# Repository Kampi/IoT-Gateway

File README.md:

# IoT-Gateway

## Table of Contents

- [IoT-Gateway](#iot-gateway)
  - [Table of Contents](#table-of-contents)
  - [About](#about)
  - [Directory Breakdown](#directory-breakdown)
  - [Building the OS](#building-the-os)
  - [Wi-Fi Configuration (nmcli)](#wi-fi-configuration-nmcli)
  - [Easy Installer Server (Raspberry Pi)](#easy-installer-server-raspberry-pi)
  - [Firmware - nRF5340 (OpenThread RCP)](#firmware---nrf5340-openthread-rcp)
  - [Firmware - nRF54L15 (Matter test light)](#firmware---nrf54l15-matter-test-light)
  - [Firmware - ESP32 LoRa (LoRaWAN test sensor)](#firmware---esp32-lora-lorawan-test-sensor)
  - [Firmware - ESP32 BLE (BLE test sensor)](#firmware---esp32-ble-ble-test-sensor)
  - [Ressources](#ressources)
  - [Maintainer](#maintainer)

## About

...

It is built with **KiCad** and integrates a full **CI/CD pipeline** using **KiBot**, ensuring reproducible outputs for documentation, manufacturing, and releases.

Key features:

- Open-source hardware design
- Automated generation of Gerber, BoM, and documentation via KiBot
- Workflow stages (DRAFT -> PRELIMINARY -> CHECKED -> RELEASED) for structured releases
- Clear documentation and changelog to track progress
- Designed with collaboration and transparency in mind

Please check the [wiki](https://github.com/Kampi/IoT-Gateway/wiki) for more information about the project.

## Directory Breakdown

- **`.github`**: GitHub related files
- **`.gitlab`**: GitLab related files
- **`.gitignore`**: Ignored files list
- **`3d-print`**: Project related files for 3D printer
- **`cad`**: Project related CAD files
- **`firmware`**: Firmware directory
- **`gateway`**: KiCad project for the PCB
- **`scripts`**: Additional scripts for CI/CD etc.
- **`CHANGELOG.md`**: Version history
- **`LICENSE`**: Project license
- **`README.md`**: Project overview

## Building the OS

The gateway OS is built with Yocto/OpenEmbedded from the `os` directory using
the provided `Makefile`.

```bash
cd os

# One-time: install the Yocto/OpenEmbedded build dependencies on this host
make setup

# Clone the Toradex BSP layers (Scarthgap / 5.0) via `repo`
make repo

# Initialize the Yocto build environment
source layers/openembedded-core/oe-init-build-env build

# Build the gateway image
bitbake gateway-os-image
```

The resulting image is located in `build/tmp/deploy/images/verdin-imx8mm/`.
Use `make clean` to remove the `.repo`/`export` checkout and the `tmp`/`deploy`
build output.

See [os/layers/meta-iot-gateway-os/README.md](os/layers/meta-iot-gateway-os/README.md)
for layer details and configuration variables.

## Wi-Fi Configuration (nmcli)

The gateway image ships with NetworkManager and its `nmcli` CLI for Wi-Fi
provisioning.

```bash
# List available Wi-Fi networks
nmcli device wifi list

# Connect to a Wi-Fi network
nmcli device wifi connect "<SSID>" password "<PASSWORD>"

# Show configured/active connections
nmcli connection show

# Check Wi-Fi radio status
nmcli radio wifi
```

## Easy Installer Server (Raspberry Pi)

`scripts/raspberry-pi/setup-tezi-server.sh` turns a Raspberry Pi (Raspberry Pi
OS / Debian 12 with NetworkManager) into the network feed for the Toradex Easy
Installer and the server for RAUC OTA bundles: a static network on `eth0`
(no default route), dnsmasq (DHCP + DNS, answers `tezi.toradex.com` with the
Pi), nginx (`/var/www/html`, bundles in `bundles/`) and an avahi announcement.
`--with-uuu` also builds `uuu` for USB recovery. It can be run again at any
time.

```bash
# on the Pi (uplink via Wi-Fi, gateway on eth0)
sudo ./setup-tezi-server.sh --with-uuu
```

Settings such as `ETH_IFACE` or `TEZI_ADDRESS` via environment variables
(`--help`). See
[os/layers/meta-iot-gateway-os/docs/tezi-feed-raspberry-pi.md](os/layers/meta-iot-gateway-os/docs/tezi-feed-raspberry-pi.md)
for the manual steps, copying images and starting the Easy Installer.

## Firmware - nRF5340 (OpenThread RCP)

`firmware/nRF5340` runs Nordic's OpenThread coprocessor (RCP) sample on the
nRF5340's network core, talking Spinel over HDLC-over-UART to `otbr-agent`
on the Verdin (UART_4). The workspace is a self-contained `west` setup -
the nRF Connect SDK is fetched on demand and never vendored into git.

```bash
cd firmware/nRF5340

# One-time: fetch the nRF Connect SDK / Zephyr workspace
make setup

# Build for the stock nRF5340-DK and flash it
make build
make flash

# Once the carrier board's schematic is final and the pin overlay updated
make build TARGET=gateway
```

See [firmware/nRF5340/README.md](firmware/nRF5340/README.md) for the full
workspace layout, prerequisites, and board overlay details.

## Firmware - nRF54L15 (Matter test light)

`firmware/device/nRF54L15_Matter` turns an nRF54L15-DK into a Matter-over-Thread
light bulb that joins the gateway's Thread network and is added to Home
Assistant via Matter. It builds against an installed nRF Connect SDK
(`~/ncs/v3.3.4` by default).

```bash
cd firmware/device/nRF54L15_Matter
make build
make erase-flash
```

See [firmware/device/nRF54L15_Matter/README.md](firmware/device/nRF54L15_Matter/README.md)
for commissioning with Home Assistant.

## Firmware - ESP32 LoRa (LoRaWAN test sensor)

`firmware/device/ESP32_LoRa` turns an ESP-WROVER-KIT with a RAK3172 module
into a LoRaWAN sensor that joins ChirpStack via OTAA (EU868, class A) through
the gateway's RAK5146 concentrator and sends a random temperature every 20 s
(deep sleep in between). PlatformIO with ESP-IDF, RAK3172 driver as git
submodule.

```bash
cd firmware/device/ESP32_LoRa
git submodule update --init components/RAK3172
pio run -e debug -t upload --upload-port /dev/ttyUSB1
```

See [firmware/device/ESP32_LoRa/README.md](firmware/device/ESP32_LoRa/README.md)
for the wiring, the OTAA keys and the ChirpStack device profile.

## Firmware - ESP32 BLE (BLE test sensor)

`firmware/device/ESP32_BLE` turns an ESP-WROVER-KIT into a BLE temperature
and humidity sensor that broadcasts BTHome v2 advertisements every 10 s.
Theengs Gateway on the gateway decodes them and publishes the sensor to Home
Assistant via MQTT discovery. PlatformIO with ESP-IDF.

```bash
cd firmware/device/ESP32_BLE
pio run -e debug -t upload --upload-port /dev/ttyUSB1
```

See [firmware/device/ESP32_BLE/README.md](firmware/device/ESP32_BLE/README.md)
for the advertisement format.

## Ressources

- [KiBot Template](https://github.com/nguyen-v/KDT_Hierarchical_KiBot)
- [KiCad Project Template](https://github.com/Kampi/Template-Project)

## Maintainer

- [Daniel Kampert](mailto:DanielKampert@kampis-elektroecke.de)

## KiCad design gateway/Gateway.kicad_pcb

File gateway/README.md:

<h1 align="center">Template</h1>

<p align="center" width="100%">
  
</p>

***

<p align="center">
  
&nbsp; &nbsp; &nbsp; &nbsp;
  
</p>

***

## SPECIFICATIONS

| Parameter | Value |
| --- | --- |
| Dimensions | 32.0 × 24.0 mm |

***

## PROJECT DIRECTORY STRUCTURE

    .
    ├─ kibot_resources       # External resources for KiBot
    │  ├─ colors             # Color theme for KiCad
    │  ├─ fonts              # Fonts used in the project
    │  ├─ scripts            # External scripts used with KiBot
    │  └─ templates          # Templates for KiBot generated reports
    ├─ kibot_yaml            # KiBot YAML config files
    ├─ Logos                 # Logos
    ├─ meta                  # Project metadata
    ├─ templates             # Title block templates
    ├─ scripts               # Project scripts
    ├─ *.kicad_sch           # KiCad schematic files
    ├─ *.kicad_pcb           # KiCad PCB layout
    ├─ *.kicad_pro           # KiCad project file
    ├─ fp-lib-table          # Project footprint libraries
    ├─ *.xml                 # Netlist of the schematic (updated by the pipeline)
    ├─ CHANGELOG.md          # Changelog of the hardware
    ├─ LICENSE               # Project license
    ├─ README.md             # Project README
    └─ kibot_launch.sh       # KiBot automation script

## OUTPUT DIRECTORY STRUCTURE

    .
    ├─ 3D                   # 3D export of the PCB (STEP)
    ├─ HTML                 # HTML files for generated webpage
    ├─ Images               # Pictures and renders
    │  └─ Logos             # Logos
    ├─ KiRI                 # KiRI (PCB diff viewer) files
    ├─ Manufacturing        # Assembly and fabrication documents
    │  ├─ Assembly          # Assembly documents (BoM, BoM check, Mouser cart, pos, notes)
    │  └─ Fabrication       # Fabrication documents (Gerber / ODB++ ZIP, notes, impedance table)
    │     ├─ Drill Tables   # CSV drill tables
    │     └─ Gerbers        # Gerbers
    ├─ Netlist              # PCB netlist
    ├─ Reports              # Reports for ERC/DRC
    ├─ Schematic            # PDF of schematic
    ├─ Testing              # Test documents
    │  └─ Testpoints        # Testpoints tables
    ├─ Variants             # Outputs for assembly variants, if available
    ├─ index.html           # Start page of the generated webpage
    └─ README.md            # This README

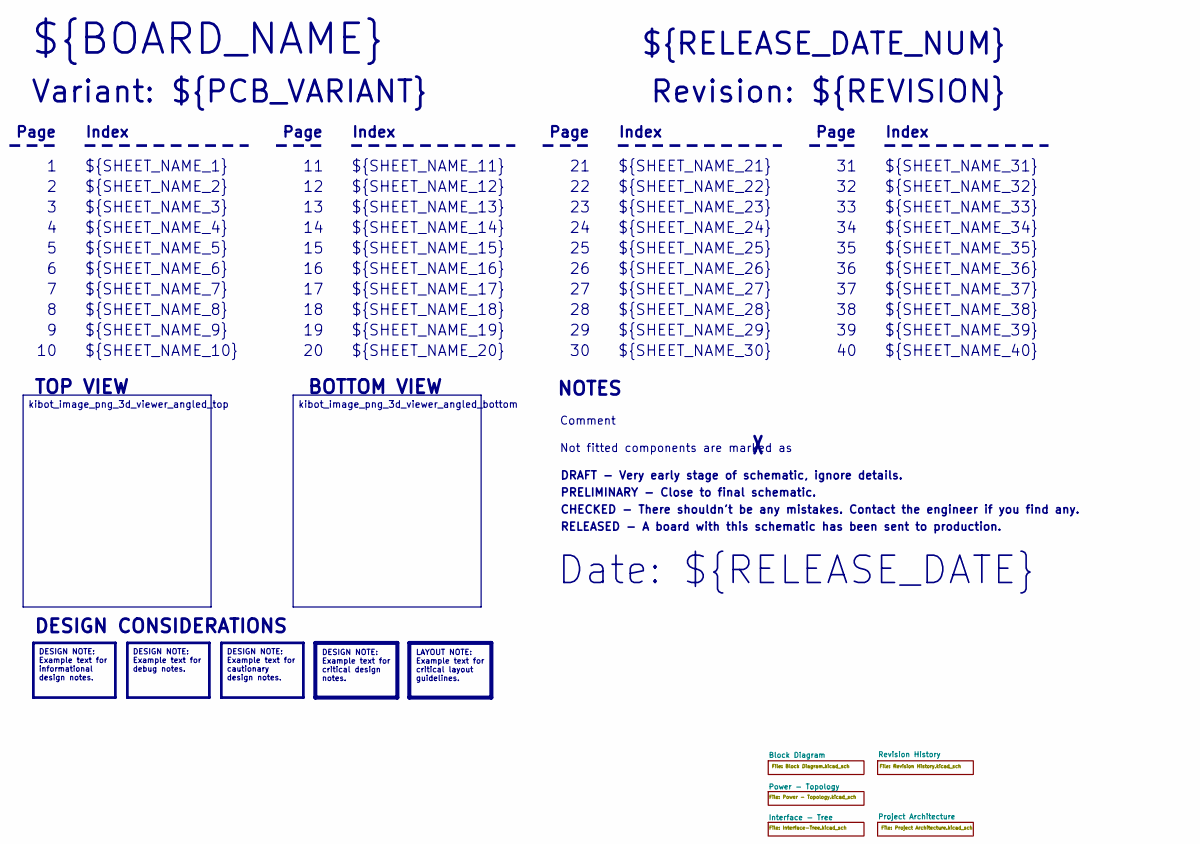
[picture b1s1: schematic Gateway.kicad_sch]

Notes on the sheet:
Variant: ${PCB_VARIANT}
RELEASED - A board with this schematic has been sent to production.
${SHEET_NAME_24}
Index
Page
PRELIMINARY - Close to final schematic.
${SHEET_NAME_22}
DRAFT - Very early stage of schematic, ignore details.
${SHEET_NAME_12}
${SHEET_NAME_8}
${SHEET_NAME_2}
${SHEET_NAME_5}
${SHEET_NAME_20}
${SHEET_NAME_23}
${RELEASE_DATE_NUM}
${SHEET_NAME_35}
Not fitted components are marked as
${SHEET_NAME_11}
${SHEET_NAME_6}
${SHEET_NAME_37}
${SHEET_NAME_26}
${SHEET_NAME_36}
Revision: ${REVISION}
${SHEET_NAME_15}
CHECKED - There shouldn't be any mistakes. Contact the engineer if you find any.
BOTTOM VIEW
${SHEET_NAME_14}
${SHEET_NAME_21}
${SHEET_NAME_17}
${SHEET_NAME_18}
Date: ${RELEASE_DATE}
${SHEET_NAME_7}
${SHEET_NAME_31}
${BOARD_NAME}
NOTES
${SHEET_NAME_40}
${SHEET_NAME_39}
${SHEET_NAME_32}
${SHEET_NAME_1}
${SHEET_NAME_9}

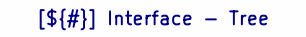
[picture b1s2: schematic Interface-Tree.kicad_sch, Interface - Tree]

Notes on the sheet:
[${#}] ${TITLE}

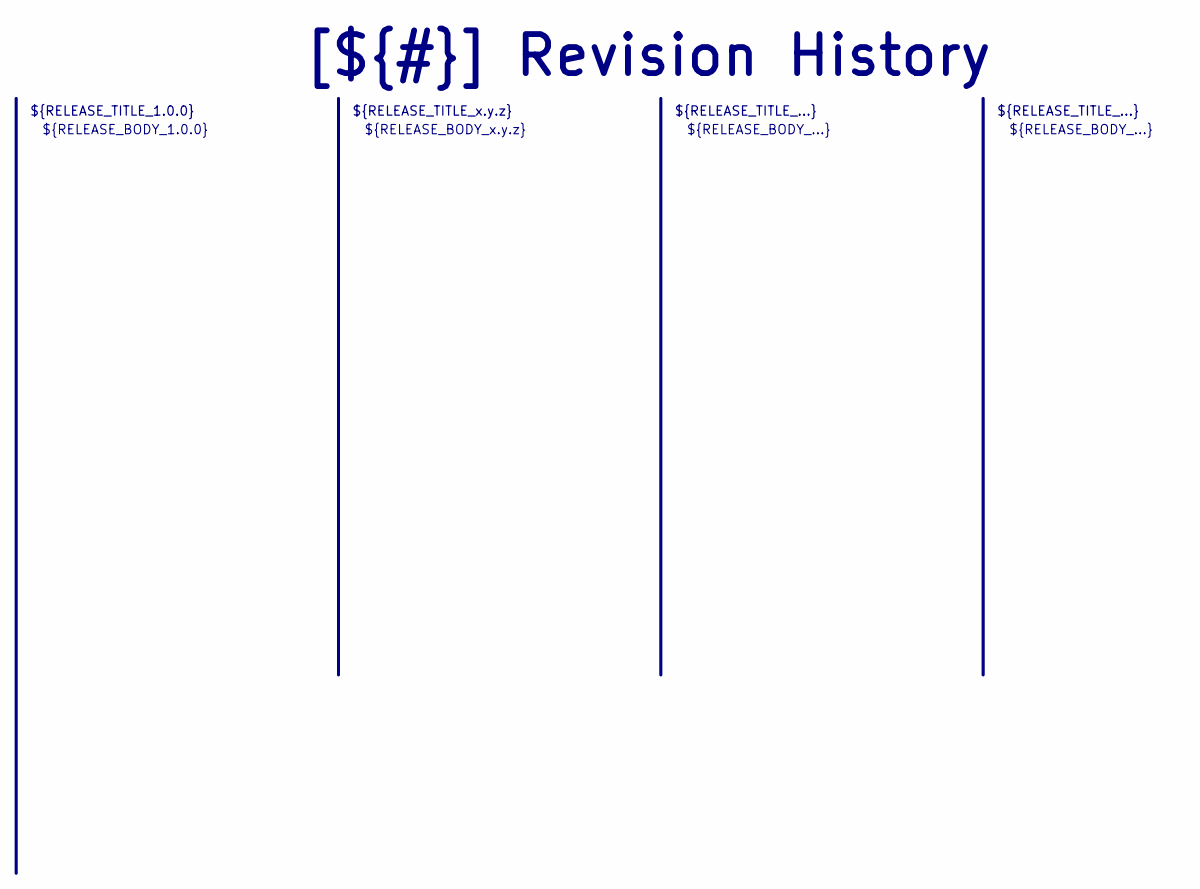
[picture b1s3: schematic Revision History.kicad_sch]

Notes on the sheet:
${RELEASE_BODY_...}
[${#}] ${TITLE}
${RELEASE_BODY_1.0.0}
${RELEASE_TITLE_...}
${RELEASE_BODY_x.y.z}
${RELEASE_TITLE_1.0.0}
${RELEASE_TITLE_x.y.z}

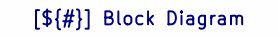
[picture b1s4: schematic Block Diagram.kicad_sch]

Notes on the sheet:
[${#}] ${TITLE}

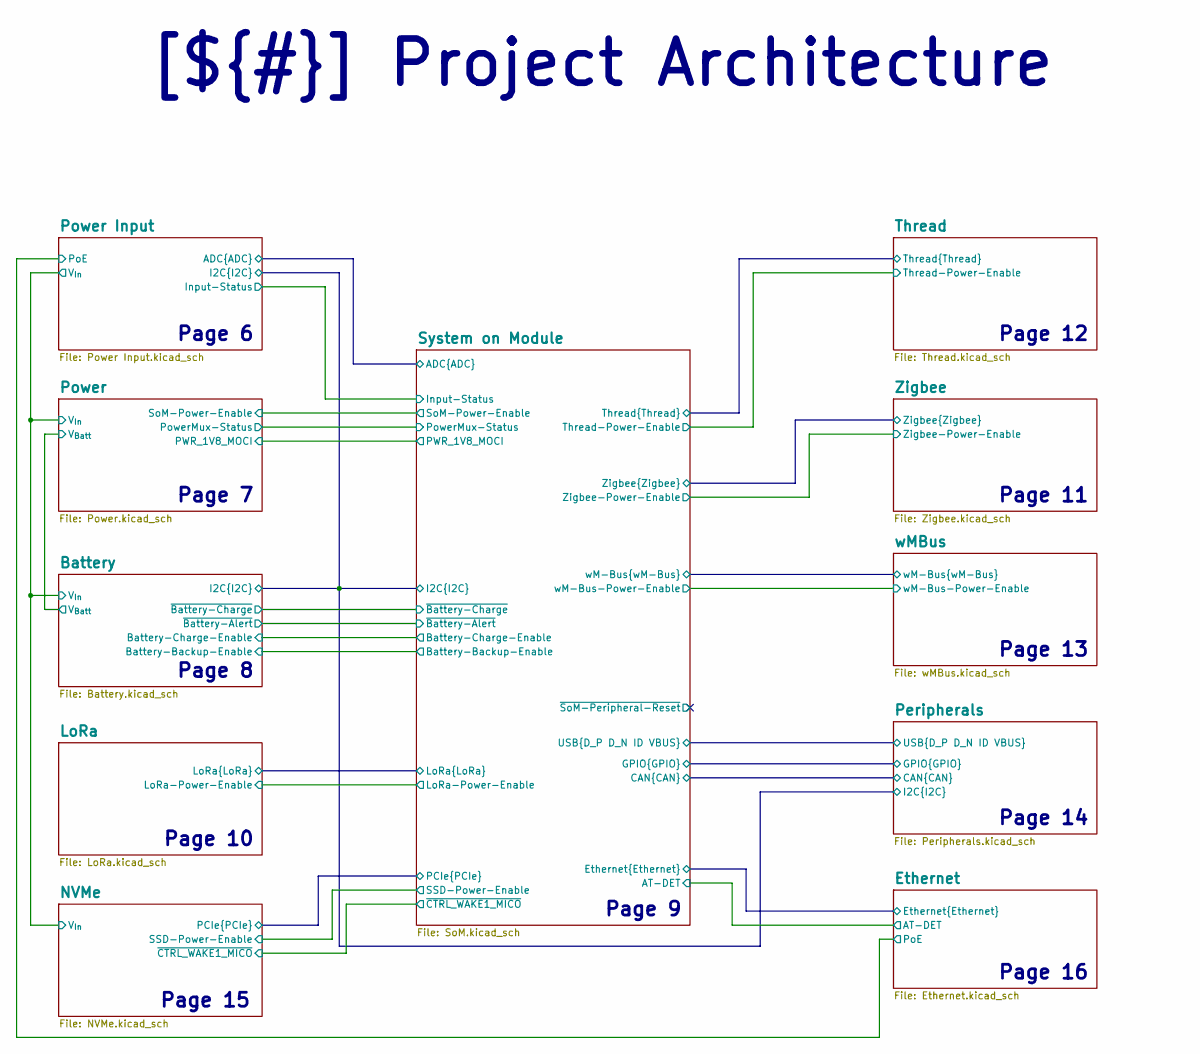
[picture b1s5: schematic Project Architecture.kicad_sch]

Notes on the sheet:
Page 13
Page 11
Page 12
Page 10
Page 14
Page 15
Page 16
Page 9
Page 6
Page 7
Page 8
[${#}] ${TITLE}

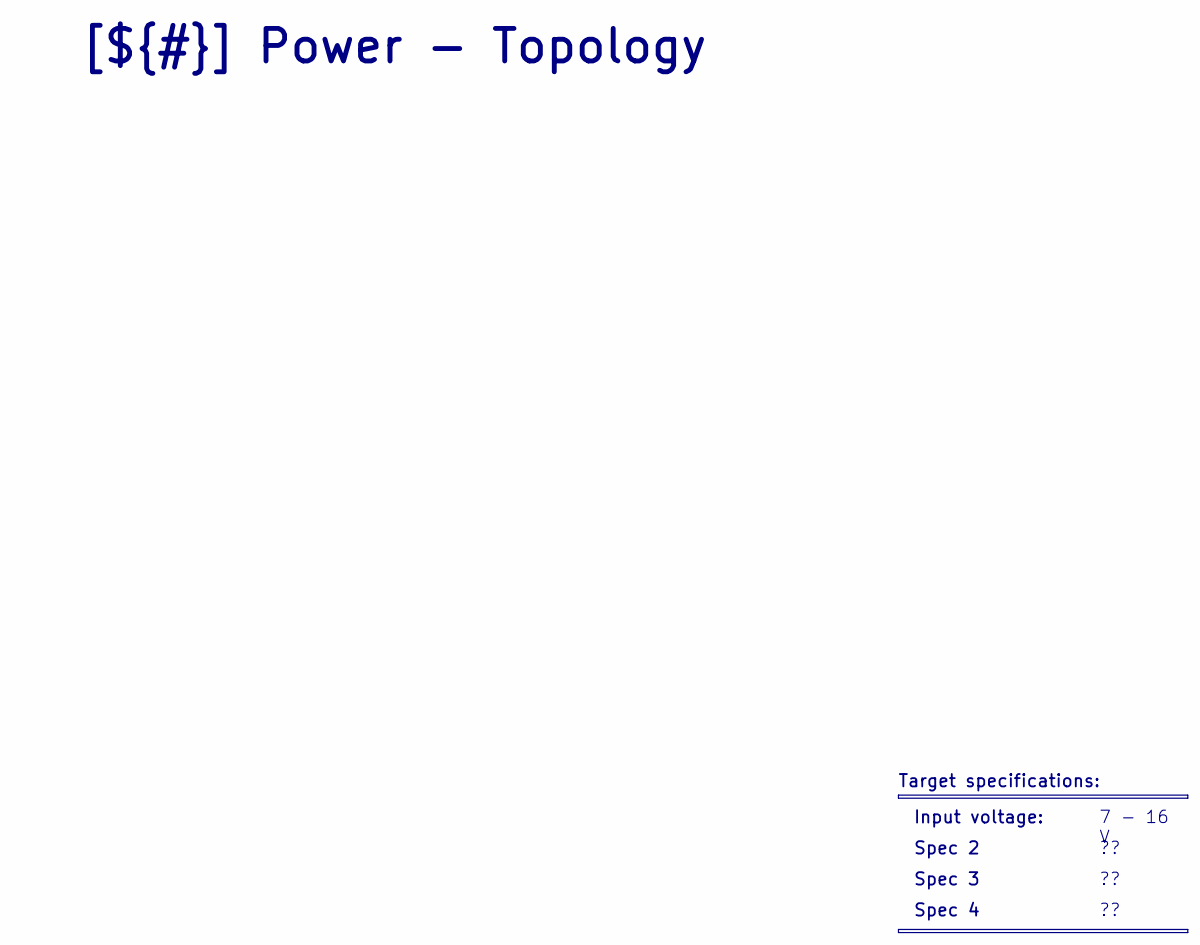
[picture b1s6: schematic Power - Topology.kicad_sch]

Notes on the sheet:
Spec 2
Input voltage:
Spec 4
7 - 16 V
Target specifications:
[${#}] ${TITLE}
Spec 3

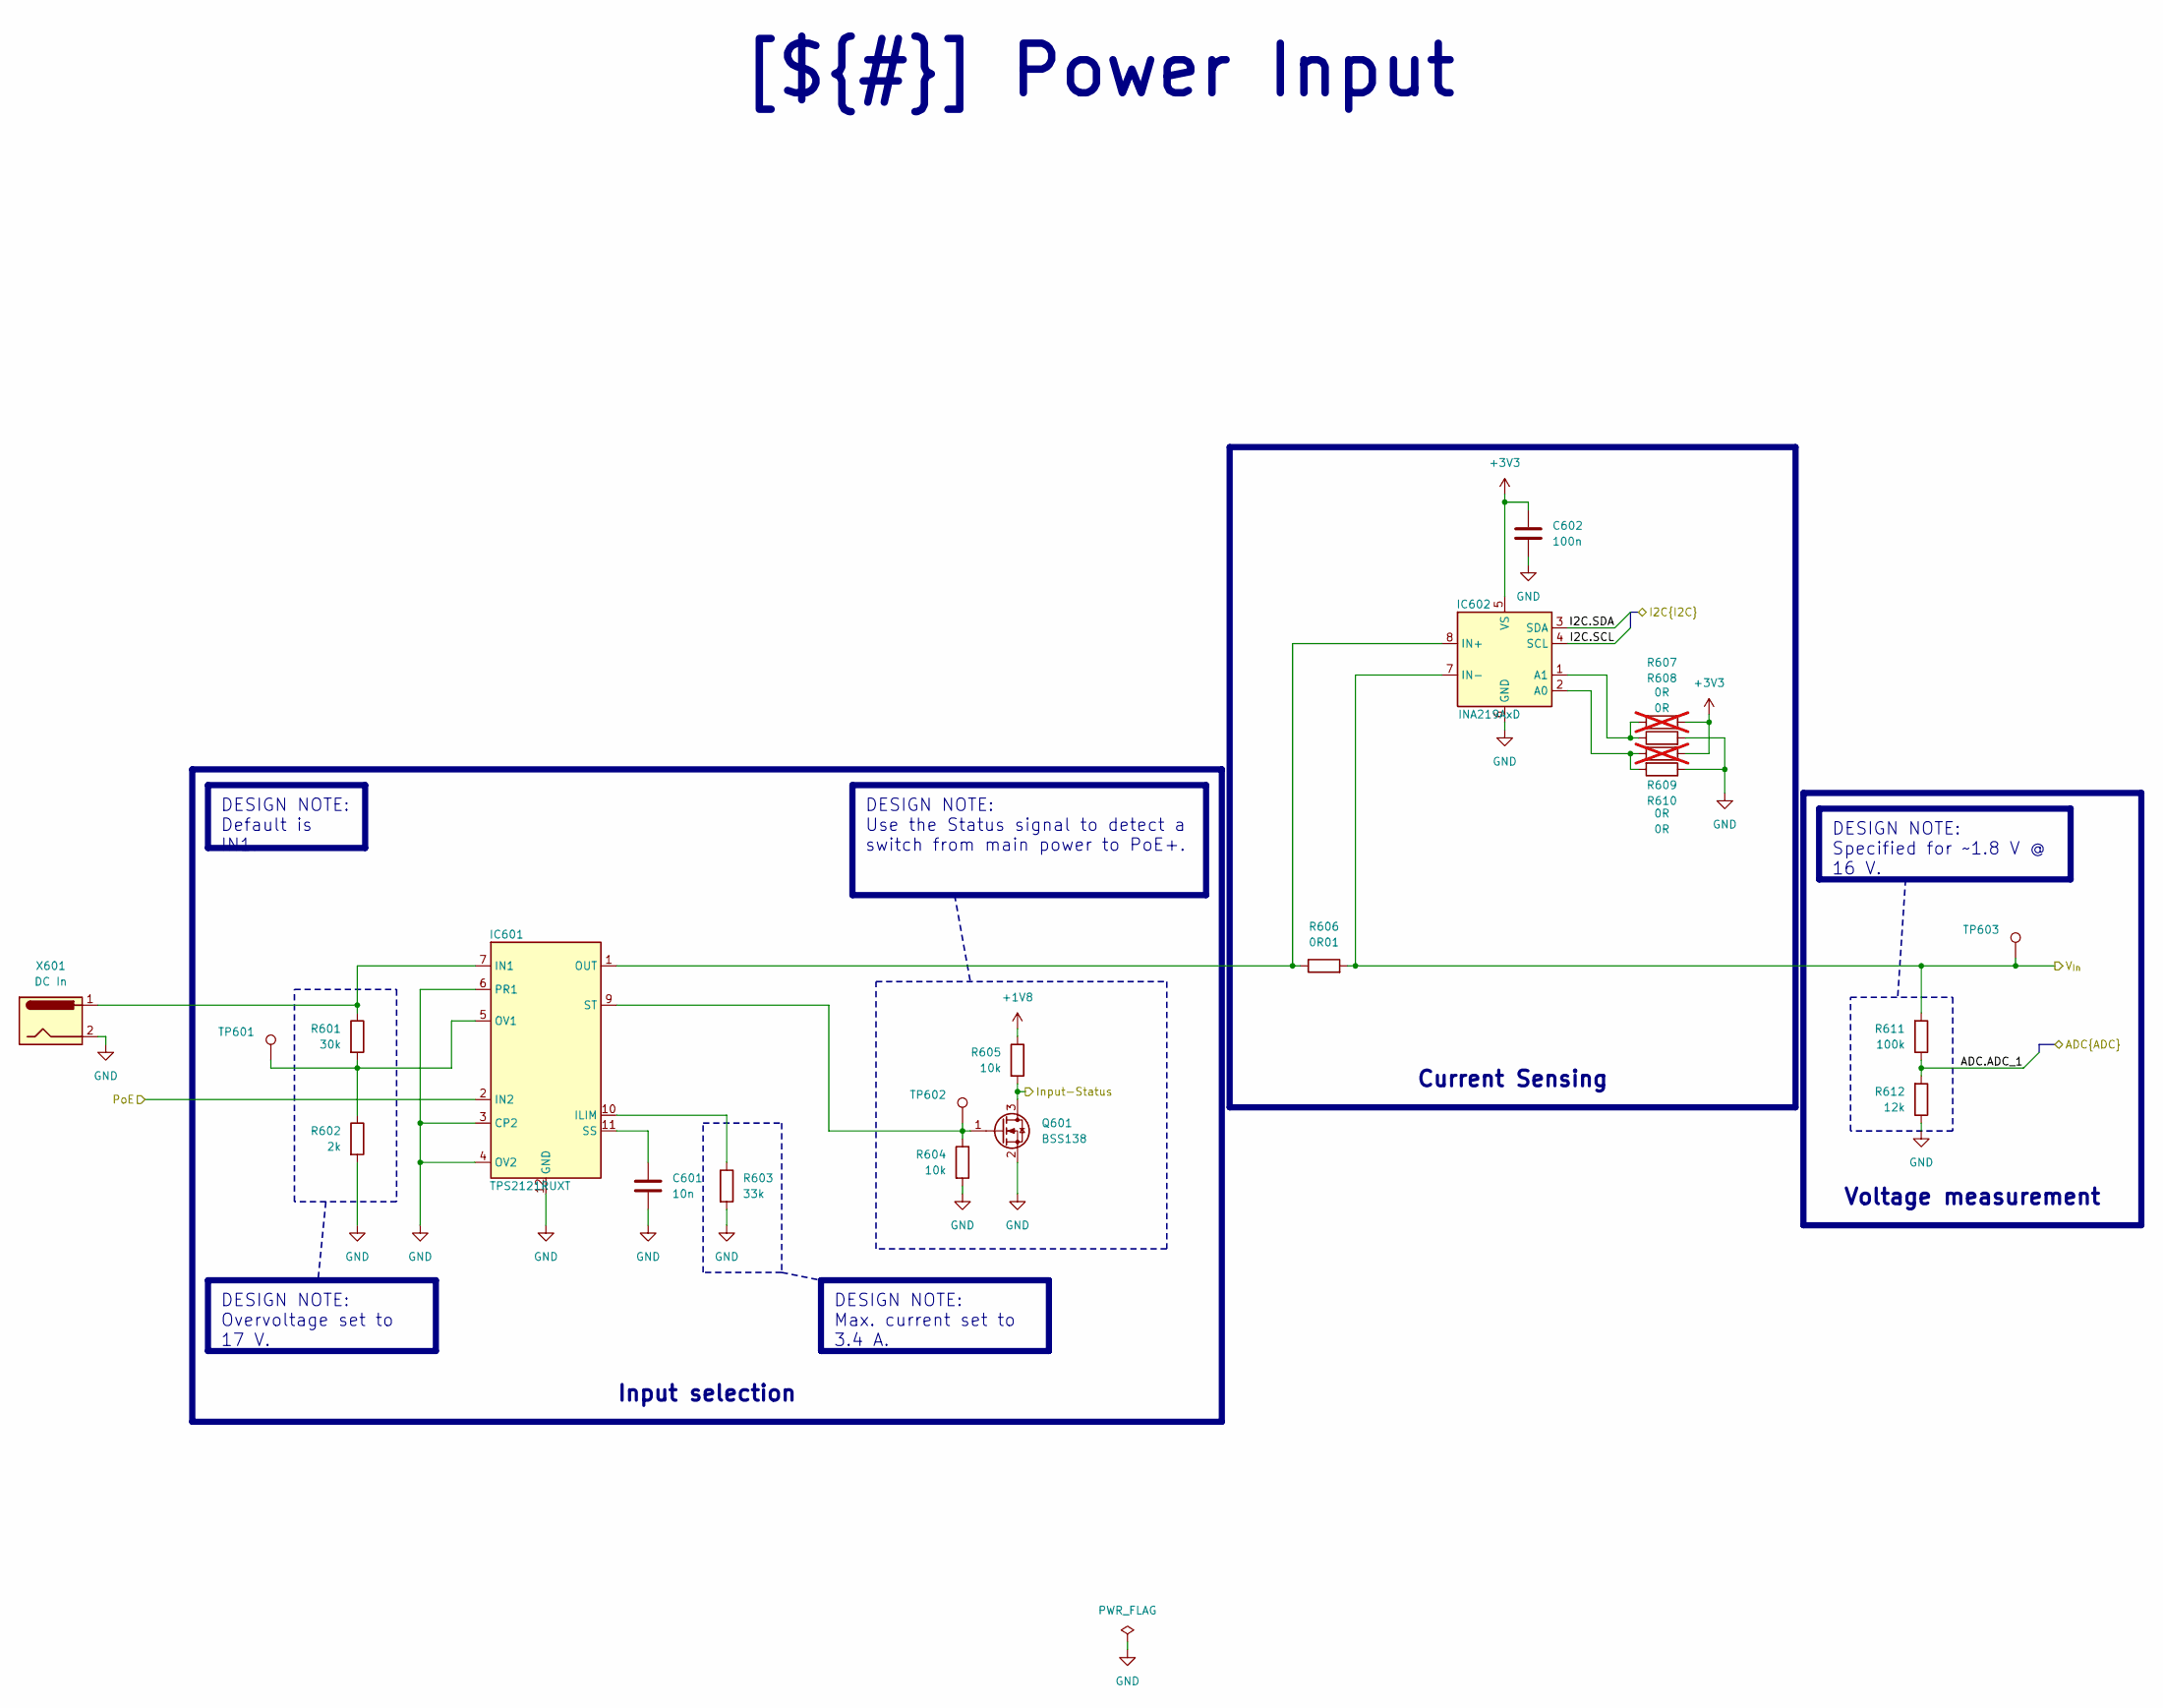
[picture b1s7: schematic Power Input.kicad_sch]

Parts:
C601: 10n; C_0805_2012Metric; mouser# 581-08055C103K4T4A
C602: 100n; C_0805_2012Metric; mouser# 581-08055C104K4Z4A
IC601: TPS2121RUXT; RUX0012A; mouser# 595-TPS2121RUXT
IC602: INA219AxD; SOIC-8_3.9x4.9mm_P1.27mm; mouser# 595-INA219BIDR
Q601: BSS138; SOT-23-3; mouser# 512-BSS138
R601: 30k; R_0805_2012Metric; mouser# 652-CR0805JW-303ELF
R602: 2k; R_0805_2012Metric; mouser# 652-CR0805FX-2001ELF
R603: 33k; R_0805_2012Metric; mouser# 652-CR0805JW-333ELF
R604, R605: 10k; R_0805_2012Metric; mouser# 652-CR0805FX-1002ELF
R606: 0R01; R_0805_2012Metric; mouser# 667-ERJ-6CWDR010V
R607, R609: 0R; R_0805_2012Metric; mouser# 652-CR0805-J/-000ELF; not fitted
R608, R610: 0R; R_0805_2012Metric; mouser# 652-CR0805-J/-000ELF
R611: 100k; R_0805_2012Metric; mouser# 603-RT0805FRE13100KL
R612: 12k; R_0805_2012Metric; mouser# 652-CR0805FX-1202ELF
TP601, TP602, TP603: TestPoint_Pad_1.0x1.0mm
X601: DC In; BarrelJack_Wuerth_6941xx301002; mouser# 710-694106301002

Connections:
+1V8: R605.1; also elsewhere on the board
+3V3: C602.1, IC602.5 (VS), R607.2, R609.1; also elsewhere on the board
/Project Architecture/Battery/I2C.SCL: IC602.4 (SCL); also elsewhere on the board
/Project Architecture/Battery/I2C.SDA: IC602.3 (SDA); also elsewhere on the board
/Project Architecture/Ethernet/PoE: IC601.2 (IN2); also elsewhere on the board
/Project Architecture/Power Input/ADC.ADC_1: R611.1, R612.2; also elsewhere on the board
/Project Architecture/Power Input/Input-Status: Q601.3 (D), R605.2; also elsewhere on the board
GND: C601.2, C602.2, IC601.3 (CP2), IC601.4 (OV2), IC601.6 (PR1), IC601.12 (GND), IC602.6 (GND), Q601.2 (S), R602.2, R603.2, R604.2, R608.2, R610.1, R612.1, X601.2; also elsewhere on the board
unnamed: IC601.10 (ILIM), R603.1
unnamed: IC601.7 (IN1), R601.1, X601.1
unnamed: IC601.5 (OV1), R601.2, R602.1, TP601.1 (1_1)
unnamed: C601.1, IC601.11 (SS)
unnamed: IC601.9 (ST), Q601.1 (G), R604.1, TP602.1 (1_1)
unnamed: IC602.2 (A0), R609.2, R610.2
unnamed: IC602.1 (A1), R607.1, R608.1
unnamed: IC601.1 (OUT), IC601.8 (OUT), IC602.8 (IN+), R606.1
V_{In}: IC602.7 (IN-), R606.2, R611.2, TP603.1 (1_1); also elsewhere on the board

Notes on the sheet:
Input selection
Voltage measurement
DESIGN NOTE: Use the Status signal to detect a switch from main power to PoE+.
[${#}] ${TITLE}
DESIGN NOTE: Default is IN1.
Current Sensing
DESIGN NOTE: Overvoltage set to 17 V.
DESIGN NOTE: Max. current set to 3.4 A.
DESIGN NOTE: Specified for ~1.8 V @ 16 V.

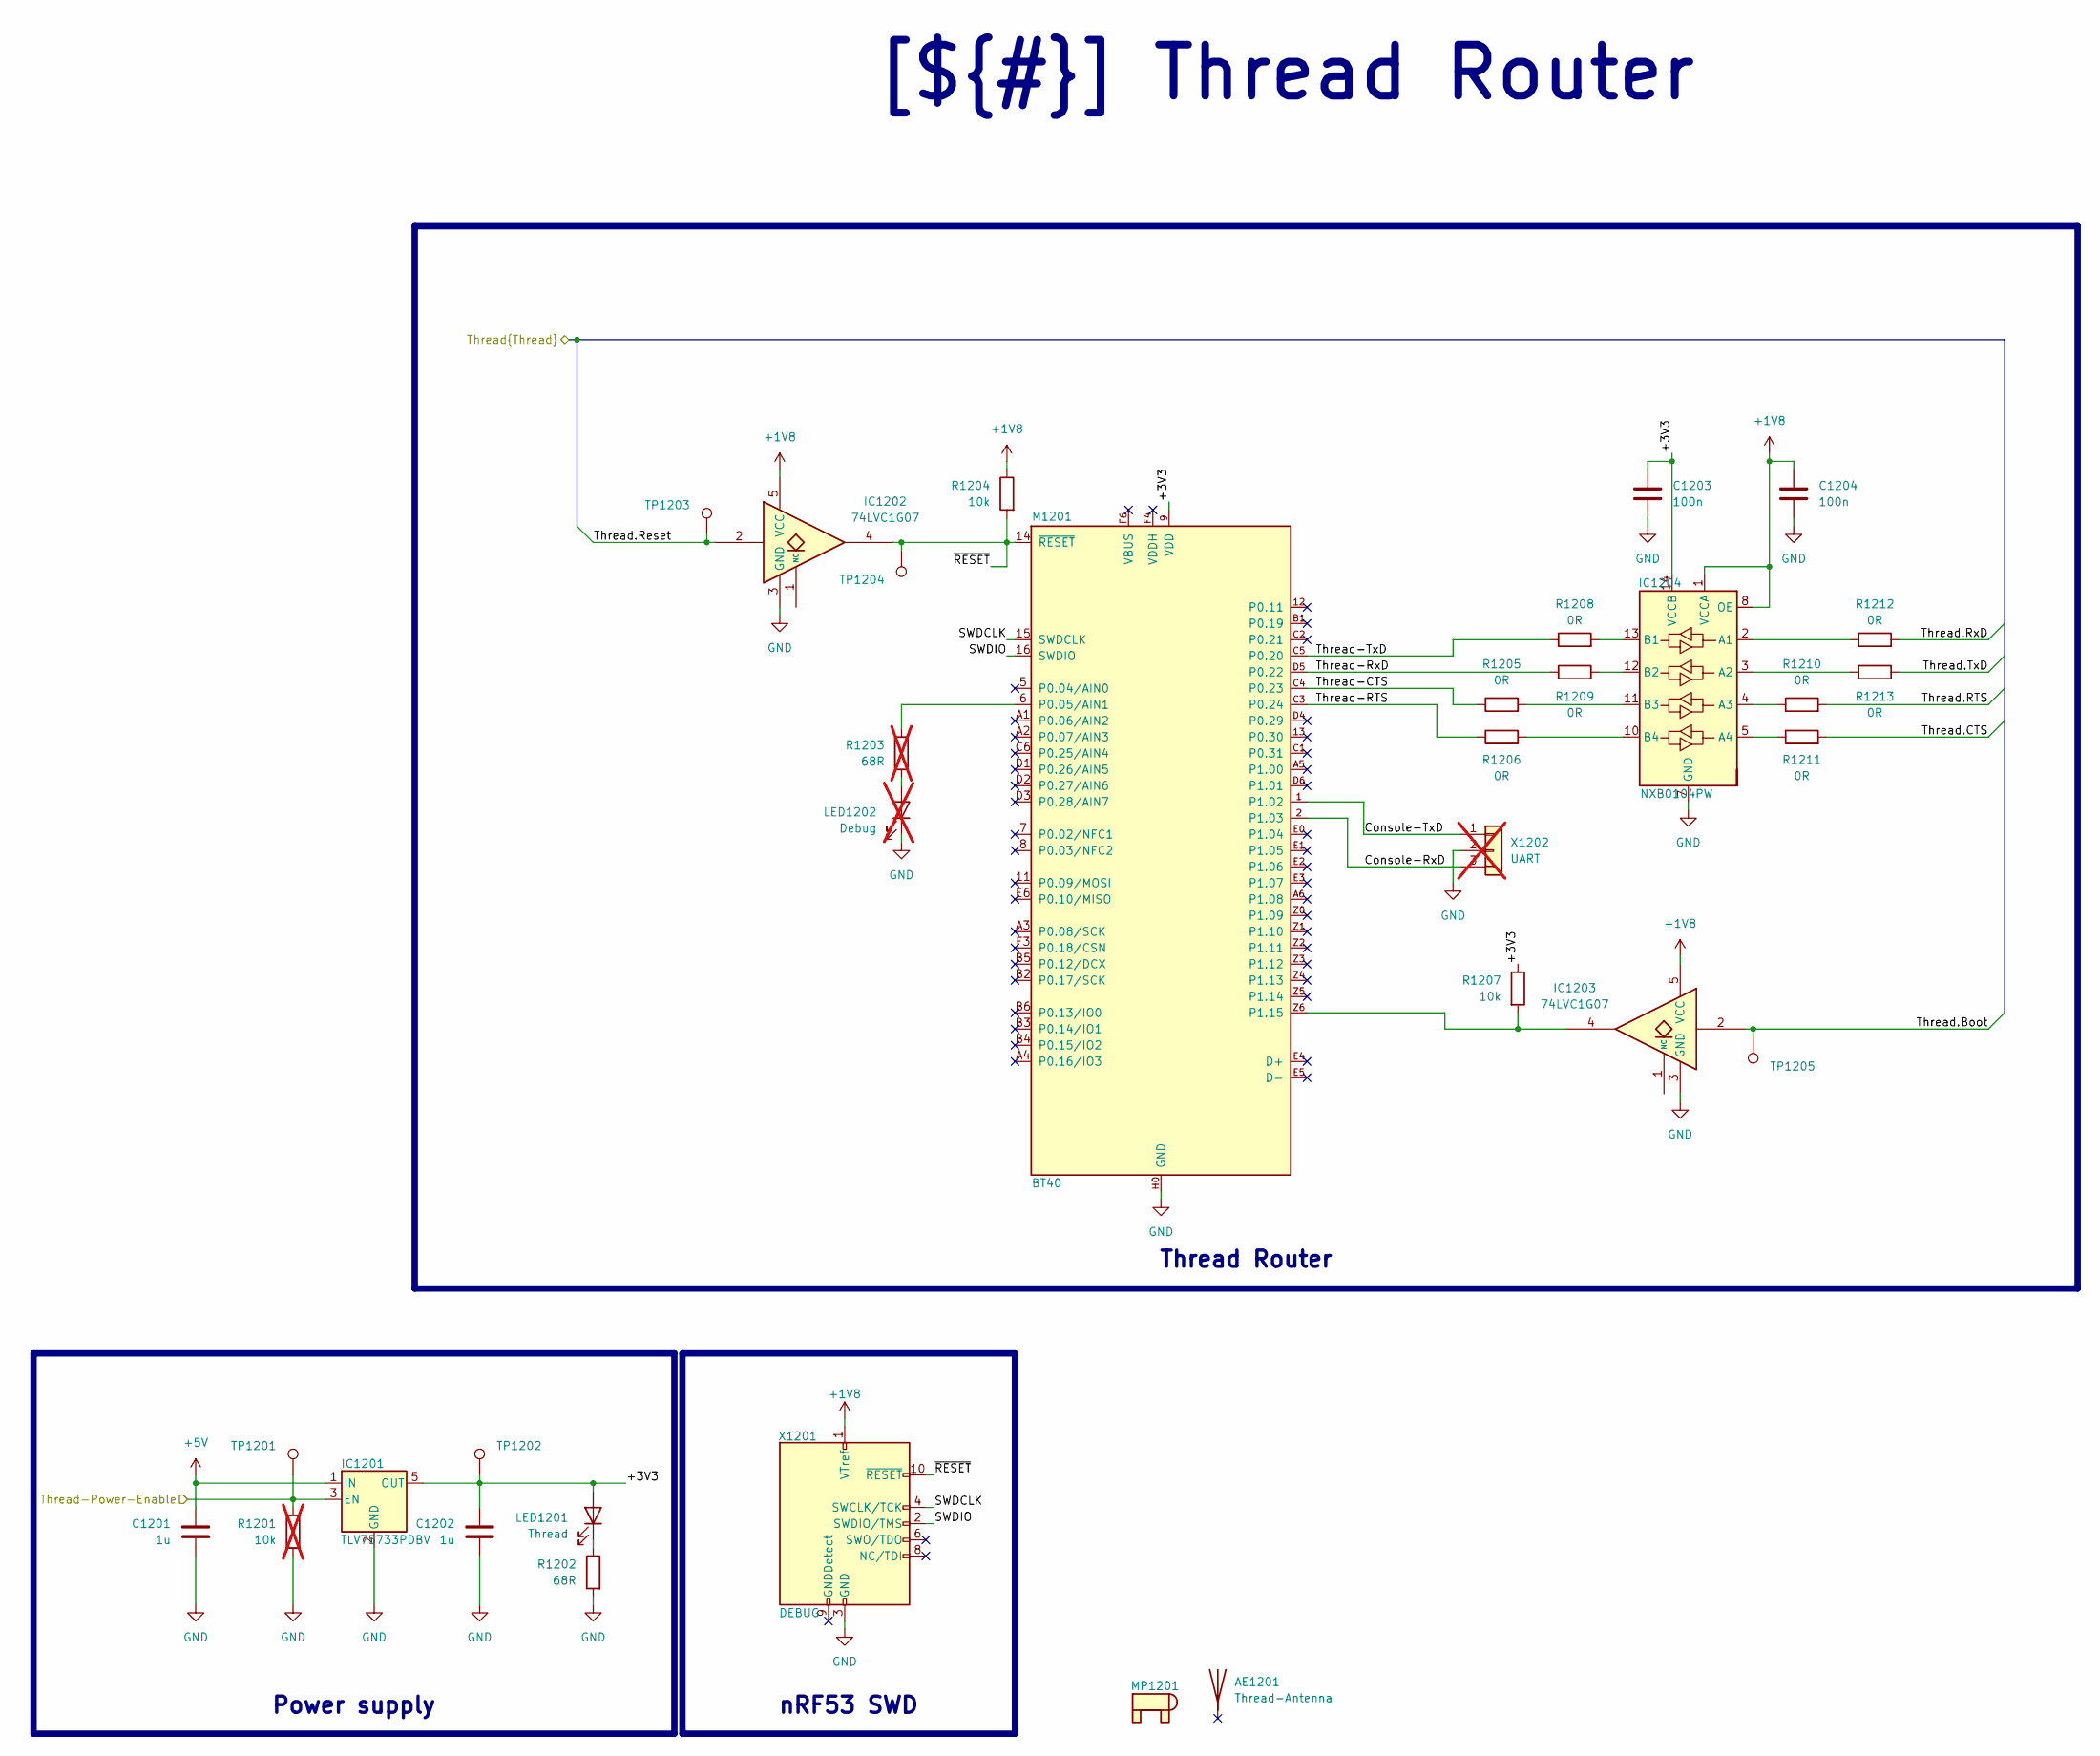
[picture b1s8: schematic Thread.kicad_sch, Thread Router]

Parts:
AE1201: Thread-Antenna
C1201, C1202: 1u; C_0805_2012Metric; mouser# 581-08053G105MAT2A
C1203, C1204: 100n; C_0805_2012Metric; mouser# 581-08055C104K4Z4A
IC1201: TLV75733PDBV; SOT-23-5; mouser# 595-TLV75733PDYDR
IC1202, IC1203: 74LVC1G07; SOT-353_SC-70-5; mouser# 771-74LVC1G07GW-G
IC1204: NXB0104PW; TSSOP-14_4.4x5mm_P0.65mm; mouser# 771-NXB0104PWJ
LED1201: Thread; LED_0805_2012Metric; mouser# 749-SM0805YC
LED1202: Debug; LED_0805_2012Metric; mouser# 749-SM0805YC; not fitted
M1201: BT40; BT40E; mouser# 308-BT40E
MP1201: SLP3-300-100-F; mouser# 749-SLP3-300-100-F
R1201: 10k; R_0805_2012Metric; mouser# 652-CR0805FX-1002ELF; not fitted
R1202: 68R; R_0805_2012Metric; mouser# 652-CR0805JW-680ELF
R1203: 68R; R_0805_2012Metric; mouser# 652-CR0805JW-680GLF; not fitted
R1204, R1207: 10k; R_0805_2012Metric; mouser# 652-CR0805FX-1002ELF
R1205, R1206, R1208, R1209, R1210, R1211, R1212, R1213: 0R; R_0805_2012Metric; mouser# 652-CR0805-J/-000ELF
TP1201, TP1202, TP1203, TP1204, TP1205: TestPoint_Pad_1.0x1.0mm
X1201: DEBUG; SHF-105-01-L-D-SM-TR; mouser# 640-BD12510A305580LB
X1202: UART; PinHeader_1x03_P2.54mm_Vertical; not fitted

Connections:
+1V8: C1204.1, IC1202.5 (VCC), IC1203.5 (VCC), IC1204.1 (VCCA), IC1204.8 (OE), R1204.1, X1201.1 (VTref); also elsewhere on the board
+5V: C1201.2, IC1201.1 (IN); also elsewhere on the board
/Project Architecture/System on Module/Thread-Power-Enable: IC1201.3 (EN), R1201.1, TP1201.1 (1_1); also elsewhere on the board
/Project Architecture/System on Module/Thread.Boot: IC1203.2, TP1205.1 (1_1); also elsewhere on the board
/Project Architecture/System on Module/Thread.CTS: R1211.2; also elsewhere on the board
/Project Architecture/System on Module/Thread.RTS: R1210.2; also elsewhere on the board
/Project Architecture/System on Module/Thread.Reset: IC1202.2, TP1203.1 (1_1); also elsewhere on the board
/Project Architecture/System on Module/Thread.RxD: R1212.2; also elsewhere on the board
/Project Architecture/System on Module/Thread.TxD: R1213.1; also elsewhere on the board
/Project Architecture/Thread/+3V3: C1202.2, C1203.1, IC1201.5 (OUT), IC1204.14 (VCCB), LED1201.2 (A), M1201.9 (VDD), R1207.1, TP1202.1 (1_1)
/Project Architecture/Thread/Console-RxD: M1201.2 (P1.03), X1202.3
/Project Architecture/Thread/Console-TxD: M1201.1 (P1.02), X1202.1
/Project Architecture/Thread/SWDCLK: M1201.15 (SWDCLK), X1201.4 (SWCLK/TCK)
/Project Architecture/Thread/SWDIO: M1201.16 (SWDIO), X1201.2 (SWDIO/TMS)
/Project Architecture/Thread/Thread-CTS: M1201.C4 (P0.23), R1205.1
/Project Architecture/Thread/Thread-RTS: M1201.C3 (P0.24), R1206.1
/Project Architecture/Thread/Thread-RxD: M1201.D5 (P0.22), R1209.2
/Project Architecture/Thread/Thread-TxD: M1201.C5 (P0.20), R1208.1
/Project Architecture/Thread/~RESET: IC1202.4, M1201.14 (~RESET), R1204.2, TP1204.1 (1_1), X1201.10 (~RESET)
GND: C1201.1, C1202.1, C1203.2, C1204.2, IC1201.2 (GND), IC1202.3 (GND), IC1203.3 (GND), IC1204.7 (GND), LED1202.1 (K), M1201.10 (GND), M1201.A0 (GND), M1201.B0 (GND), M1201.C0 (GND), M1201.D0 (GND), M1201.H0 (GND), M1201.H1 (GND), M1201.H2 (GND), M1201.H3 (GND), R1201.2, R1202.2, X1201.3 (GND), X1201.5 (GND), X1202.2; also elsewhere on the board
unnamed: IC1204.2 (A1), R1212.1
unnamed: IC1204.3 (A2), R1213.2
unnamed: IC1204.4 (A3), R1210.1
unnamed: IC1204.5 (A4), R1211.1
unnamed: IC1204.13 (B1), R1208.2
unnamed: IC1204.12 (B2), R1209.1
unnamed: IC1204.11 (B3), R1205.2
unnamed: IC1204.10 (B4), R1206.2
unnamed: LED1201.1 (K), R1202.1
unnamed: LED1202.2 (A), R1203.2
unnamed: M1201.6 (P0.05/AIN1), R1203.1
unnamed: IC1203.4, M1201.Z6 (P1.15), R1207.2

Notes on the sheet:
Thread Router
nRF53 SWD
[${#}] ${TITLE}
Power supply

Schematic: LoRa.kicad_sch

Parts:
AE1001: LoRa-Antenna
C1001, C1002: 1u; C_0805_2012Metric; mouser# 581-08053G105MAT2A
H1001, H1002: MountingHole; 9774015151R; mouser# 710-9774015151R
IC1001: TLV75733PDBV; SOT-23-5; mouser# 595-TLV75733PDYDR
IC1002: 74LVC1G07; SOT-353_SC-70-5; mouser# 771-74LVC1G07GW-G
LED1001: LoRa; LED_0805_2012Metric; mouser# 749-SM0805YC
MP1001: SLP3-300-100-F; mouser# 749-SLP3-300-100-F
R1001: 10k; R_0805_2012Metric; mouser# 652-CR0805FX-1002ELF; not fitted
R1002: 68R; R_0805_2012Metric; mouser# 652-CR0805JW-680ELF
R1003: 10k; R_0805_2012Metric; mouser# 652-CR0805FX-1002ELF
TP1001, TP1002, TP1003: TestPoint_Pad_1.0x1.0mm
X1001: LoRa; BUS_PCI_Express_Mini_Full; mouser# 538-67910-5700

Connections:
+1V8: IC1002.5 (VCC); also elsewhere on the board
+5V: C1001.2, IC1001.1 (IN); also elsewhere on the board
/Project Architecture/LoRa/+3V3: C1002.2, IC1001.5 (OUT), LED1001.2 (A), R1003.1, TP1002.1 (1_1), X1001.2 (+3V3AUX), X1001.24 (+3V3AUX), X1001.39 (+3V3AUX), X1001.41 (+3V3AUX), X1001.52 (+3V3AUX)
/Project Architecture/LoRa/LoRa-Power-Enable: IC1001.3 (EN), R1001.1, TP1001.1 (1_1); also elsewhere on the board
/Project Architecture/LoRa/LoRa.D_N: X1001.36 (USB_D-); also elsewhere on the board
/Project Architecture/LoRa/LoRa.D_P: X1001.38 (USB_D+); also elsewhere on the board
/Project Architecture/LoRa/LoRa.Reset: IC1002.2, TP1003.1 (1_1); also elsewhere on the board
GND: C1001.1, C1002.1, IC1001.2 (GND), IC1002.3 (GND), R1001.2, R1002.2, X1001.4 (GND), X1001.9 (GND), X1001.15 (GND), X1001.18 (GND), X1001.21 (GND), X1001.26 (GND), X1001.27 (GND), X1001.29 (GND), X1001.34 (GND), X1001.35 (GND), X1001.37 (GND), X1001.40 (GND), X1001.43 (GND), X1001.50 (GND), X1001.MP; also elsewhere on the board
unnamed: LED1001.1 (K), R1002.1
unnamed: IC1002.4, R1003.2, X1001.13 (REFCLK+)

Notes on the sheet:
[${#}] ${TITLE}
Power supply
LoRa Concentrator

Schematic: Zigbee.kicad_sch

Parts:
AE1101: Zigbee-Antenna
C1101, C1102: 1u; C_0805_2012Metric; mouser# 581-08053G105MAT2A
C1103, C1104, C1105: 100n; C_0805_2012Metric; mouser# 581-08055C104K4Z4A
C1106: 10u; C_0805_2012Metric; mouser# 581-KGM21FS61E106KU
IC1101: TLV75733PDBV; SOT-23-5; mouser# 595-TLV75733PDYDR
IC1102: TXB0102DCU; VSSOP-8_2.3x2mm_P0.5mm; mouser# 595-TXB0102DCUR
IC1103, IC1104: 74LVC1G07; SOT-353_SC-70-5; mouser# 771-74LVC1G07GW-G
LED1101: Zigbee; LED_0805_2012Metric; mouser# 749-SM0805YC
M1101: RF-BM-2652
MP1101: SLP3-300-100-F; mouser# 749-SLP3-300-100-F
R1101: 10k; R_0805_2012Metric; mouser# 652-CR0805FX-1002ELF; not fitted
R1102, R1103, R1105, R1106: 0R; R_0805_2012Metric; mouser# 652-CR0805-J/-000ELF
R1104: 68R; R_0805_2012Metric; mouser# 652-CR0805JW-680ELF
R1107, R1108: 10k; R_0805_2012Metric; mouser# 652-CR0805FX-1002ELF
TP1101, TP1102, TP1103, TP1104: TestPoint_Pad_1.0x1.0mm

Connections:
+1V8: C1103.1, IC1102.3 (VCCA), IC1102.6 (OE), IC1103.5 (VCC), IC1104.5 (VCC); also elsewhere on the board
+5V: C1101.2, IC1101.1 (IN); also elsewhere on the board
/Project Architecture/System on Module/Zigbee-Power-Enable: IC1101.3 (EN), R1101.1, TP1101.1 (1_1); also elsewhere on the board
/Project Architecture/System on Module/Zigbee.Boot: IC1104.2, TP1104.1 (1_1); also elsewhere on the board
/Project Architecture/System on Module/Zigbee.Reset: IC1103.2, TP1103.1 (1_1); also elsewhere on the board
/Project Architecture/System on Module/Zigbee.RxD: R1103.1; also elsewhere on the board
/Project Architecture/System on Module/Zigbee.TxD: R1102.1; also elsewhere on the board
/Project Architecture/Zigbee/+3V3: C1102.2, C1104.1, C1105.2, C1106.1, IC1101.5 (OUT), IC1102.7 (VCCB), LED1101.2 (A), M1101.13 (VCC), R1107.1, R1108.1, TP1102.1 (1_1)
/Project Architecture/Zigbee/CC2652-RxD: M1101.8 (DIO12), R1105.2
/Project Architecture/Zigbee/CC2652-TxD: M1101.9 (DIO13), R1106.2
GND: C1101.1, C1102.1, C1103.2, C1104.2, C1105.1, C1106.2, IC1101.2 (GND), IC1102.2 (GND), IC1103.3 (GND), IC1104.3 (GND), M1101.14 (GND), M1101.29 (GND), R1101.2, R1104.2; also elsewhere on the board
unnamed: IC1102.5 (A1), R1102.2
unnamed: IC1102.4 (A2), R1103.2
unnamed: IC1102.8 (B1), R1105.1
unnamed: IC1102.1 (B2), R1106.1
unnamed: LED1101.1 (K), R1104.1
unnamed: IC1104.4, M1101.16 (DIO15), R1108.2
unnamed: IC1103.4, M1101.10 (~RESET), R1107.2

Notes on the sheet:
Zigbee Coordinator
[${#}] ${TITLE}
DESIGN NOTE: Use version with on-board antenna connector.
Power supply

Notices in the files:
README.md:
License: MIT 3.0
